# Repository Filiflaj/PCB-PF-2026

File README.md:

# PF 2026 - Sparkling LED Greeting Card

A custom-designed PCB created as a unique "Pour Féliciter 2026" (Happy New Year 2026) greeting card. The board features **39 individually addressable LEDs** arranged to form the text "PF 26", displaying a dynamic, warm fireworks sparkling effect.

This project is built around the **ATmega328P-AU** microcontroller, making it fully compatible with the Arduino ecosystem.

---

## 📷 Preview

*Finished and assembled PCB with the sparkling effect.*

---

## ⚡ Technical Specifications

* **MCU:** ATmega328P-AU (8-bit AVR, 16MHz external crystal).
* **LEDs:** 39x WS2812B-2020 (NeoPixel) in a single chain.
* **LED Pin:** Connected to **PD3** (Digital Pin **3** in Arduino IDE).
* **Interfaces:** * Standard **ICSP** header (for bootloader and ISP programming).
    * **UART** header (RX, TX, VCC, GND, DTR) for serial communication and programming.
* **Power:** 5V via USB-C connector (with 5.1k CC resistors for compatibility).

---

## 📂 Project Structure

The repository is divided into two main sections:

### 🛠️ [HW-PF-2026](./HW-PF-2026) (Hardware)
Contains all files necessary for PCB manufacturing and assembly:
* **KiCad Project:** Full schematic and PCB layout files.
* **Schematic:** PDF version for quick reference.
* **Manufacturing:** Gerbers and Drill files.
* **BOM:** Bill of Materials.

### 💻 [FW-PF-2026](./FW-PF-2026) (Firmware)
Contains the Arduino source code:
* **Sparkle Effect:** A gentle, warm-yellow "fireworks" animation with random 1-3 LED bursts and a dim static background.
* **Library dependency:** Requires the `Adafruit_NeoPixel` library.

---

## 🔌 Programming Guide

Since the board does not have an onboard USB-to-Serial converter, you can program it using an **Arduino UNO R3** as an ISP programmer.

### 1. Wiring (Arduino UNO to ICSP)

Connect your Arduino UNO to the ICSP header on the PF 2026 board as follows:

| Arduino UNO (Programmer) | PF 2026 (Target) |
| :--- | :--- |
| 5V | VCC |
| GND | GND |
| Pin 13 | SCK |
| Pin 12 | MISO |
| Pin 11 | MOSI |
| **Pin 10** | **RESET** |

### 2. Burning the Bootloader
1.  Open Arduino IDE.
2.  Go to **File -> Examples -> 11.ArduinoISP -> ArduinoISP** and upload it to your UNO.
3.  Go to **Tools -> Board** and select **Arduino Uno**.
4.  Go to **Tools -> Programmer** and select **Arduino as ISP**.
5.  Click **Tools -> Burn Bootloader**.

### 3. Uploading Firmware
1.  Open the sketch from the `/FW-PF-2026` folder.
2.  Go to **Sketch -> Upload Using Programmer** (or press `Ctrl+Shift+U`).

---

## 👤 Author
**Filip Flajšinger** Created for the 2026 New Year celebrations. 🥂

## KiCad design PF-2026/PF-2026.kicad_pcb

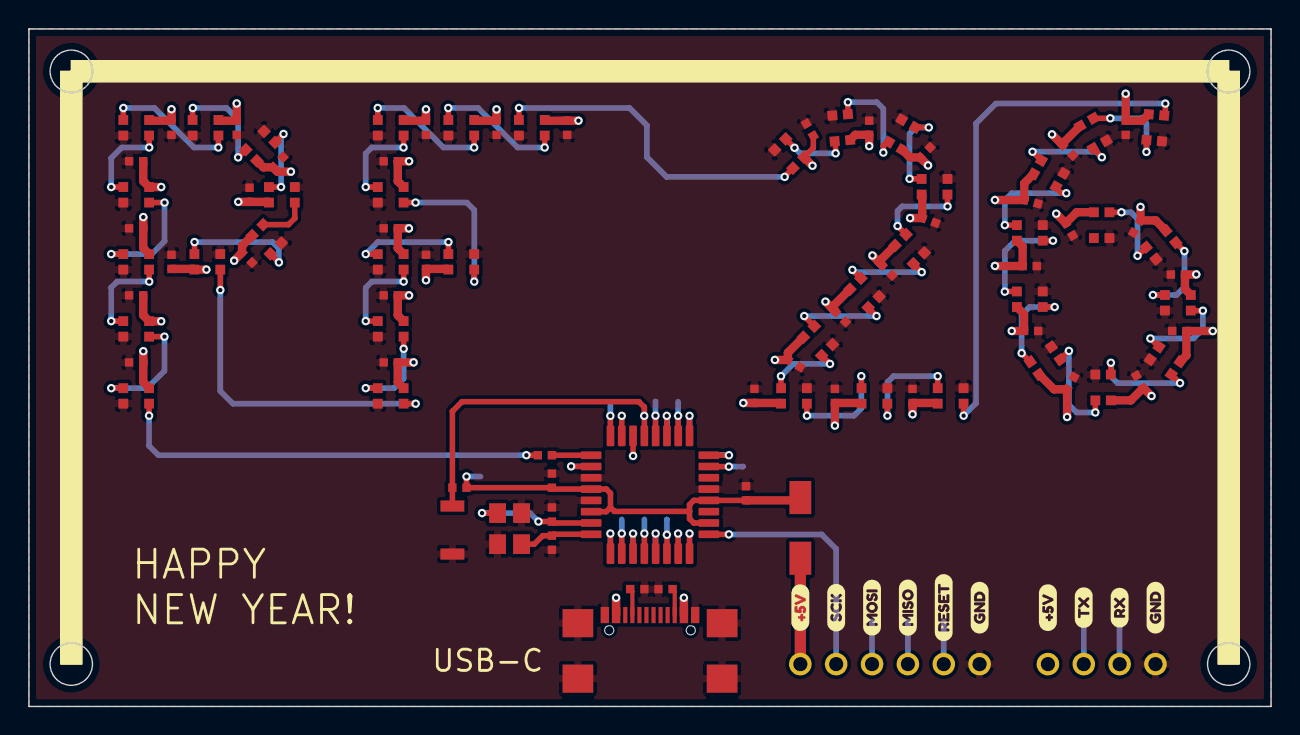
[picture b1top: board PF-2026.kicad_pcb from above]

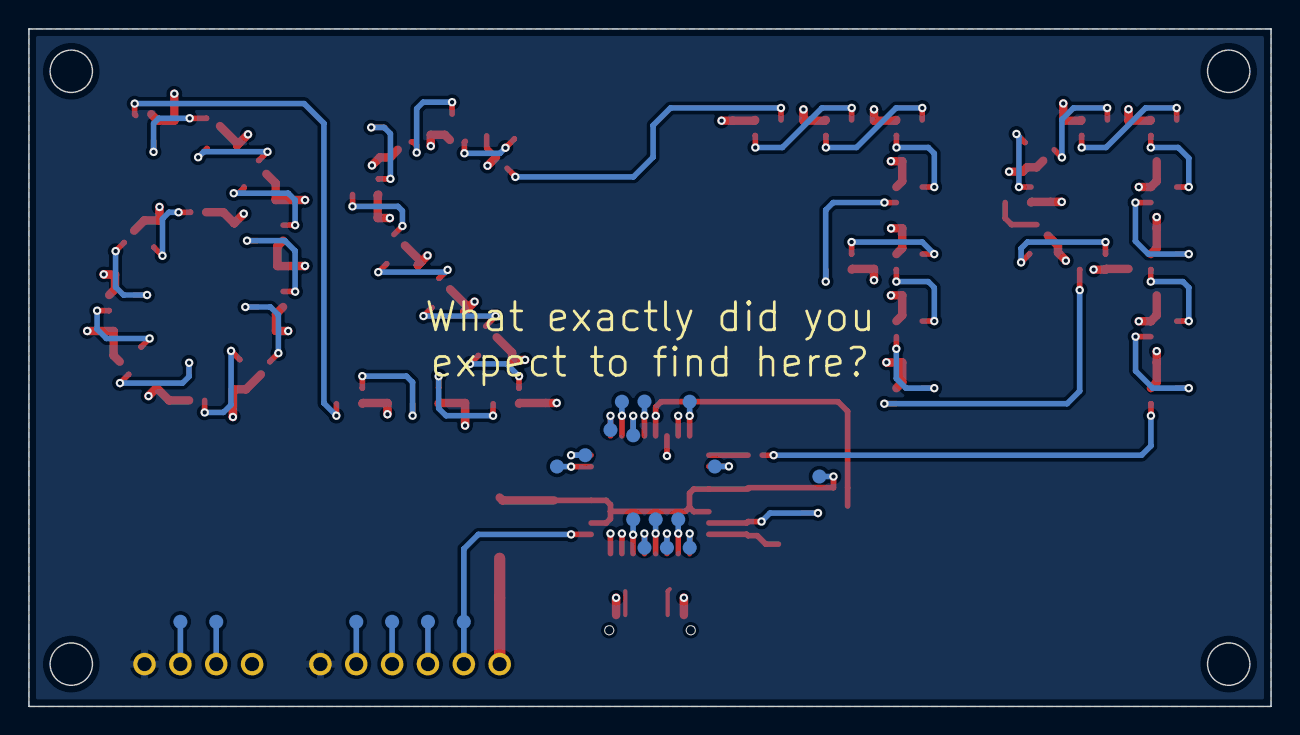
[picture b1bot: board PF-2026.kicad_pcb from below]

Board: 4 copper layers, 88.0 x 48.0 mm, 124 parts (21 on the bottom side), 67 nets.

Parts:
C1, C2, C5, C6, C7, C8, C9, C10, C11, C12, C13, C14, C15, C16, C17, C18, C19, C20, C21, C22, C23, C24, C25, C26, C27, C28, C29, C30, C31, C32, C33, C34, C35, C36, C37, C38, C39, C40, C41, C42, C43: 100nF; CAPACITOR-0402_R
C3, C4: 18pF/50V; CAPACITOR-0402_R
D2: SS14; SS14_R
JP1: ICSP; HEADER-6-PIN-THT
JP2: USB4110GFA; USB4110GFA_R
JP3: HEADER-4-PIN-THT
LED1, LED2, LED3, LED4, LED5, LED6, LED7, LED8, LED9, LED10, LED11, LED12, LED13, LED14, LED15, LED16, LED17, LED18, LED19, LED20, LED21, LED22, LED23, LED24, LED25, LED26, LED27, LED28, LED29, LED30, LED31, LED32, LED33, LED34, LED35, LED36, LED37, LED38, LED39: WS2812B-2020; WS2812B-2020_R
R1: 10k; RESISTOR-0402_R
R2, R3: 5k1; RESISTOR-0402_R
R4: 330R; RESISTOR-0402_R
S1: B3U-1000P; B3U-1000P_R
TP1, TP2, TP3, TP4, TP5, TP6, TP7, TP8, TP9, TP10, TP11, TP12, TP14, TP15, TP16, TP17, TP18, TP19, TP20, TP21, TP22: TP-1.0-MM
U1: ATMEGA328P-AU; ATMEGA328P-AU_R
Y1: ABM8-16.000MHZ; ABM8-16.000MHZ-7-1-U-T_R
kibuzzard-69414ECA, kibuzzard-69414ECA#2: G***; kibuzzard-69414ECA
kibuzzard-69414EE3: G***; kibuzzard-69414EE3
kibuzzard-69414EEA: G***; kibuzzard-69414EEA
kibuzzard-69414EF3, kibuzzard-69414EF3#2: G***; kibuzzard-69414EF3
kibuzzard-69414F1E: G***; kibuzzard-69414F1E
kibuzzard-69414F2A: G***; kibuzzard-69414F2A
kibuzzard-69414F2F: G***; kibuzzard-69414F2F
kibuzzard-69414F25: G***; kibuzzard-69414F25

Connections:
+5V: C5.1, C6.1, C7.1, C8.1, C9.1, C10.1, C11.1, C12.1, C13.1, C14.1, C15.1, C16.1, C17.1, C18.1, C19.1, C20.1, C21.1, C22.1, C23.1, C24.1, C25.1, C26.1, C27.1, C28.1, C29.1, C30.1, C31.1, C32.1, C33.1, C34.1, C35.1, C36.1, C37.1, C38.1, C39.1, C40.1, C41.1, C42.1, C43.1, D2.2, JP1.1, JP2.A4/B9 (VBUS), JP2.B4/A9 (VBUS), JP3.1, LED1.4 (VDD), LED2.4 (VDD), LED3.4 (VDD), LED4.4 (VDD), LED5.4 (VDD), LED6.4 (VDD), LED7.4 (VDD), LED8.4 (VDD), LED9.4 (VDD), LED10.4 (VDD), LED11.4 (VDD), LED12.4 (VDD), LED13.4 (VDD), LED14.4 (VDD), LED15.4 (VDD), LED16.4 (VDD), LED17.4 (VDD), LED18.4 (VDD), LED19.4 (VDD), LED20.4 (VDD), LED21.4 (VDD), LED22.4 (VDD), LED23.4 (VDD), LED24.4 (VDD), LED25.4 (VDD), LED26.4 (VDD), LED27.4 (VDD), LED28.4 (VDD), LED29.4 (VDD), LED30.4 (VDD), LED31.4 (VDD), LED32.4 (VDD), LED33.4 (VDD), LED34.4 (VDD), LED35.4 (VDD), LED36.4 (VDD), LED37.4 (VDD), LED38.4 (VDD), LED39.4 (VDD)
/MCU/AD0: TP4.0, U1.23 (PC0)
/MCU/AD1: TP5.0, U1.24 (PC1)
/MCU/AD2: TP6.0, U1.25 (PC2)
/MCU/AD3: TP7.0, U1.26 (PC3)
/MCU/IO2: TP12.0, U1.32 (PD2)
/MCU/IO4: TP14.0, U1.2 (PD4)
/MCU/IO5: TP15.0, U1.9 (PD5)
/MCU/IO6: TP16.0, U1.10 (PD6)
/MCU/IO7: TP17.0, U1.11 (PD7)
/MCU/IO8: TP1.0, U1.12 (PB0)
/MCU/IO9: TP2.0, U1.13 (PB1)
/MCU/IO10: TP3.0, U1.14 (PB2)
/MCU/MISO: JP1.4, TP20.0, U1.16 (PB4/MISO)
/MCU/MOSI: JP1.3, TP19.0, U1.15 (PB3/MOSI)
/MCU/RESET: JP1.5, R1.1, S1.2, TP18.0, U1.29 (PC6/~RESET)
/MCU/RXD: JP3.3, TP11.0, U1.31 (PD1/TXD)
/MCU/SCK: JP1.2, TP21.0, U1.17 (PB5/SCK)
/MCU/SCL: TP9.0, U1.28 (PC5)
/MCU/SDA: TP8.0, U1.27 (PC4)
/MCU/TXD: JP3.2, TP10.0, U1.30 (PD0/RXD)
GND: C1.2, C2.2, C3.2, C4.2, C5.2, C6.2, C7.2, C8.2, C9.2, C10.2, C11.2, C12.2, C13.2, C14.2, C15.2, C16.2, C17.2, C18.2, C19.2, C20.2, C21.2, C22.2, C23.2, C24.2, C25.2, C26.2, C27.2, C28.2, C29.2, C30.2, C31.2, C32.2, C33.2, C34.2, C35.2, C36.2, C37.2, C38.2, C39.2, C40.2, C41.2, C42.2, C43.2, JP1.6, JP2.A1/B12 (GND), JP2.B1/A12 (GND), JP2.S1 (GND), JP2.S2 (GND), JP2.S3 (GND), JP2.S4 (GND), JP3.4, LED1.2 (GND), LED2.2 (GND), LED3.2 (GND), LED4.2 (GND), LED5.2 (GND), LED6.2 (GND), LED7.2 (GND), LED8.2 (GND), LED9.2 (GND), LED10.2 (GND), LED11.2 (GND), LED12.2 (GND), LED13.2 (GND), LED14.2 (GND), LED15.2 (GND), LED16.2 (GND), LED17.2 (GND), LED18.2 (GND), LED19.2 (GND), LED20.2 (GND), LED21.2 (GND), LED22.2 (GND), LED23.2 (GND), LED24.2 (GND), LED25.2 (GND), LED26.2 (GND), LED27.2 (GND), LED28.2 (GND), LED29.2 (GND), LED30.2 (GND), LED31.2 (GND), LED32.2 (GND), LED33.2 (GND), LED34.2 (GND), LED35.2 (GND), LED36.2 (GND), LED37.2 (GND), LED38.2 (GND), LED39.2 (GND), R2.2, R3.2, S1.1, U1.3 (GND), U1.5 (GND), U1.21 (GND), Y1.2 (GND1), Y1.4 (GND2)
IO3: R4.1, U1.1 (PD3)
LED: LED28.1 (DO), LED29.3 (DI)
unnamed: JP2.A5 (CC1), R3.1
unnamed: JP2.B5 (CC2), R2.1
unnamed: LED1.3 (DI), R4.2
unnamed: LED1.1 (DO), LED2.3 (DI)
unnamed: LED2.1 (DO), LED3.3 (DI)
unnamed: LED3.1 (DO), LED4.3 (DI)
unnamed: LED4.1 (DO), LED5.3 (DI)
unnamed: LED5.1 (DO), LED6.3 (DI)
unnamed: LED6.1 (DO), LED7.3 (DI)
unnamed: LED7.1 (DO), LED8.3 (DI)
unnamed: LED8.1 (DO), LED9.3 (DI)
unnamed: LED9.1 (DO), LED10.3 (DI)
unnamed: LED10.1 (DO), LED11.3 (DI)
unnamed: LED11.1 (DO), LED12.3 (DI)
unnamed: LED12.1 (DO), LED13.3 (DI)
unnamed: LED13.1 (DO), LED14.3 (DI)
unnamed: LED14.1 (DO), LED15.3 (DI)
unnamed: LED15.1 (DO), LED16.3 (DI)
unnamed: LED16.1 (DO), LED17.3 (DI)
unnamed: LED17.1 (DO), LED18.3 (DI)
unnamed: LED18.1 (DO), LED19.3 (DI)
unnamed: LED19.1 (DO), LED20.3 (DI)
unnamed: LED20.1 (DO), LED21.3 (DI)
unnamed: LED21.1 (DO), LED22.3 (DI)
unnamed: LED22.1 (DO), LED23.3 (DI)
unnamed: LED23.1 (DO), LED24.3 (DI)
unnamed: LED24.1 (DO), LED25.3 (DI)
unnamed: LED25.1 (DO), LED26.3 (DI)
unnamed: LED26.1 (DO), LED27.3 (DI)
unnamed: LED27.1 (DO), LED28.3 (DI)
unnamed: LED29.1 (DO), LED30.3 (DI)
unnamed: LED30.1 (DO), LED31.3 (DI)
unnamed: LED31.1 (DO), LED32.3 (DI)
unnamed: LED32.1 (DO), LED33.3 (DI)
unnamed: LED33.1 (DO), LED34.3 (DI)
unnamed: LED34.1 (DO), LED35.3 (DI)
unnamed: LED35.1 (DO), LED36.3 (DI)
unnamed: LED36.1 (DO), LED37.3 (DI)
unnamed: LED37.1 (DO), LED38.3 (DI)
unnamed: LED38.1 (DO), LED39.3 (DI)
unnamed: C1.1, C2.1, D2.1, R1.2, TP22.0, U1.4 (VCC), U1.6 (VCC), U1.18 (AVCC), U1.20 (AREF)
unnamed: C4.1, U1.7 (PB6/XTAL1), Y1.3 (Y2)
unnamed: C3.1, U1.8 (PB7/XTAL2), Y1.1 (Y1)

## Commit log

2025-12-15 Create KiCad project
2025-12-15 Edit project schematic and create PCB
2025-12-16 Finalise PCB design
2026-01-06 Restructure the project, Add FW
2026-01-06 Edit ReadMe
